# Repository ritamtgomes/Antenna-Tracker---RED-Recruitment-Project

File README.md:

# ESP32 Antenna Tracker

## Overview
This project is a **PCB-based antenna tracker** originally developed as a recruitment project for the **Rocket Experiment Division (RED)** at Instituto Superior Técnico. 

The system is designed to track a flying rocket in real time and orient an antenna towards it, minimizing telemetry loss during launches and flight operations. Tracking is achieved by computing the relative azimuth and elevation angles between the ground station and the rocket, and actuating two servo motors accordingly.

## System Architecture
1. The rocket transmits its position to the ground station
2. The tracker’s local GPS module provides its own position
3. The ESP32 computes Azimuth amd Elevation and converts these angles into PWM signals
4. The two servo motors rotate the antenna to maintain alignment with the rocket

## Hardware Specifications

### Core Components
- **Microcontroller**: ESP32-C3 SoC (Wi-Fi / Bluetooth capable)
- **GPS Module**: u-blox NEO-M9N-00B
- **Actuators**: 2 × High-torque servo motors (azimuth & elevation)
- **RF Receiver**: RFD868x (or compatible)
- **Power**: 2S Li-ion battery (7.4 V)
- On-board 5 V and 3.3 V regulation

### PCB
- Designed in KiCad
- Dimensions: 75 × 55 mm
- All components placed on the top layer

## Current Status
- **Hardware design**: Completed
- **PCB layout**: Ongoing improvements and minor revisions
- **Firmware**: In development
- **Assembly & testing**: Pending

## Future Improvements
- Improved PCB routing 
- Redundant antenna configurations (directional + omnidirectional)
- MAVLink integration

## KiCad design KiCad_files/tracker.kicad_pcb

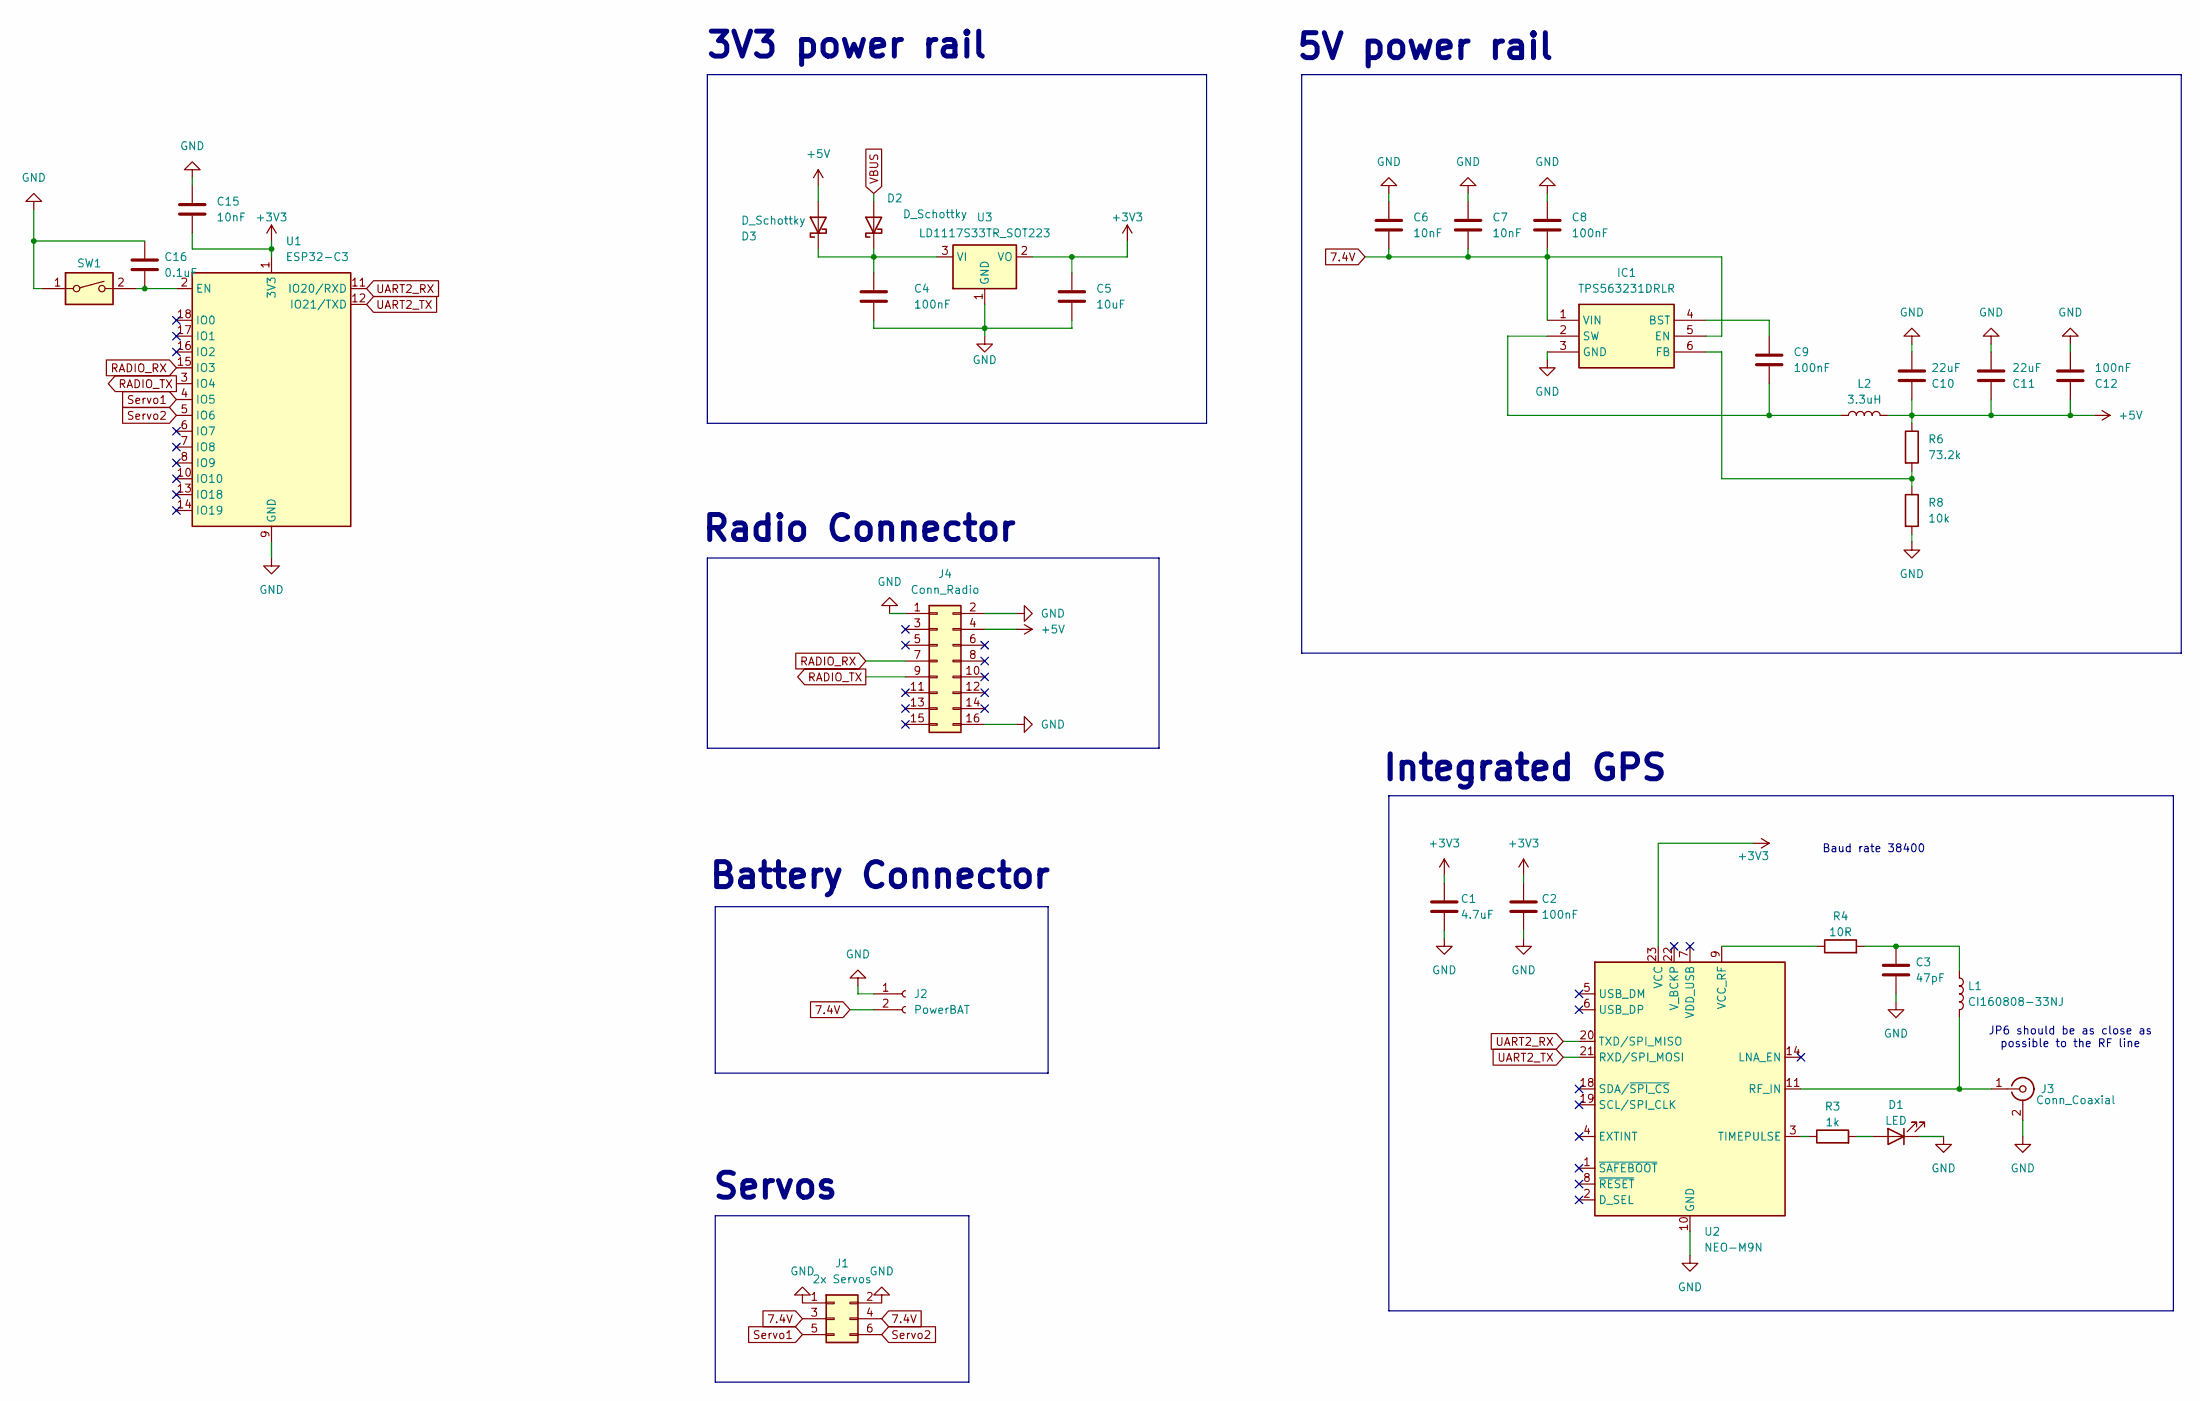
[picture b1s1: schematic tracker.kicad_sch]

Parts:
C1: 4.7uF; C_1206_3216Metric
C2, C4: 100nF; C_1206_3216Metric
C3: 47pF; C_1206_3216Metric
C5: 10uF; C_1206_3216Metric
C6, C7, C15: 10nF; C_0805_2012Metric_Pad1.18x1.45mm_HandSolder
C8, C9, C12: 100nF; C_0805_2012Metric_Pad1.18x1.45mm_HandSolder
C10, C11: 22uF; C_0805_2012Metric_Pad1.18x1.45mm_HandSolder
C16: 0.1uF; C_0805_2012Metric_Pad1.18x1.45mm_HandSolder
D1: LED; LED_1206_3216Metric
D2, D3: D_Schottky; D_0805_2012Metric_Pad1.15x1.40mm_HandSolder
IC1: TPS563231DRLR; SOTFL50P160X60-6N; Manufacturer_Part_Number TPS563231DRLR
J1: 2x Servos; PinHeader_2x03_P2.54mm_Horizontal
J2: PowerBAT; AMASS_XT30UPB-F_1x02_P5.0mm_Vertical
J3: Conn_Coaxial; U.FL_Molex_MCRF_73412-0110_Vertical
J4: Conn_Radio; PinSocket_2x08_P2.54mm_Vertical_SMD
L1: CI160808-33NJ; L_0603_1608Metric_Pad1.05x0.95mm_HandSolder
L2: 3.3uH; L_Vishay_IHLP-2020
R3: 1k; R_1206_3216Metric
R4: 10R; R_1206_3216Metric
R6: 73.2k; R_0402_1005Metric_Pad0.72x0.64mm_HandSolder
R8: 10k; R_0402_1005Metric_Pad0.72x0.64mm_HandSolder
SW1: SW_Push_1P1T_NO_CK_KSC6xxJ
U1: ESP32-C3; ESP32-C3-WROOM-02
U2: NEO-M9N; ublox_NEO
U3: LD1117S33TR_SOT223; SOT-223-3_TabPin2

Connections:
7.4V: C6.2, C7.2, C8.2, IC1.1 (VIN), IC1.5 (EN), J1.3, J1.4, J2.2
+3V3: C1.1, C2.1, C5.1, C15.2, U1.1 (3V3), U2.23 (VCC), U3.2 (VO)
+5V: C10.1, C11.1, C12.1, D3.2 (A), J4.4, L2.2, R6.1
GND: C1.2, C2.2, C3.2, C4.2, C5.2, C6.1, C7.1, C8.1, C10.2, C11.2, C12.2, C15.1, C16.2, D1.1 (K), IC1.3 (GND), J1.1, J1.2, J2.1, J3.2 (Ext), J4.1, J4.2, J4.16, R8.2, SW1.1, U1.9 (GND), U1.19 (GND), U2.10 (GND), U2.12 (GND), U2.13 (GND), U2.24 (GND), U3.1 (GND)
unnamed: C3.1, L1.1, R4.2
unnamed: D1.2 (A), R3.2
unnamed: C4.1, D2.1 (K), D3.1 (K), U3.3 (VI)
unnamed: C9.1, IC1.4 (BST)
unnamed: IC1.6 (FB), R6.2, R8.1
unnamed: C9.2, IC1.2 (SW), L2.1
unnamed: J3.1 (In), L1.2, U2.11 (RF_IN)
unnamed: C16.1, SW1.2, U1.2 (EN)
unnamed: R3.1, U2.3 (TIMEPULSE)
unnamed: R4.1, U2.9 (VCC_RF)
RADIO_RX: J4.7, U1.15 (IO3)
RADIO_TX: J4.9, U1.3 (IO4)
Servo1: J1.5, U1.4 (IO5)
Servo2: J1.6, U1.5 (IO6)
UART2_RX: U1.11 (IO20/RXD), U2.20 (TXD/SPI_MISO)
UART2_TX: U1.12 (IO21/TXD), U2.21 (RXD/SPI_MOSI)
VBUS: D2.2 (A)

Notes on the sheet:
Integrated GPS
Servos
Baud rate 38400
JP6 should be as close as possible to the RF line
3V3 power rail
Radio Connector
5V power rail
Battery Connector

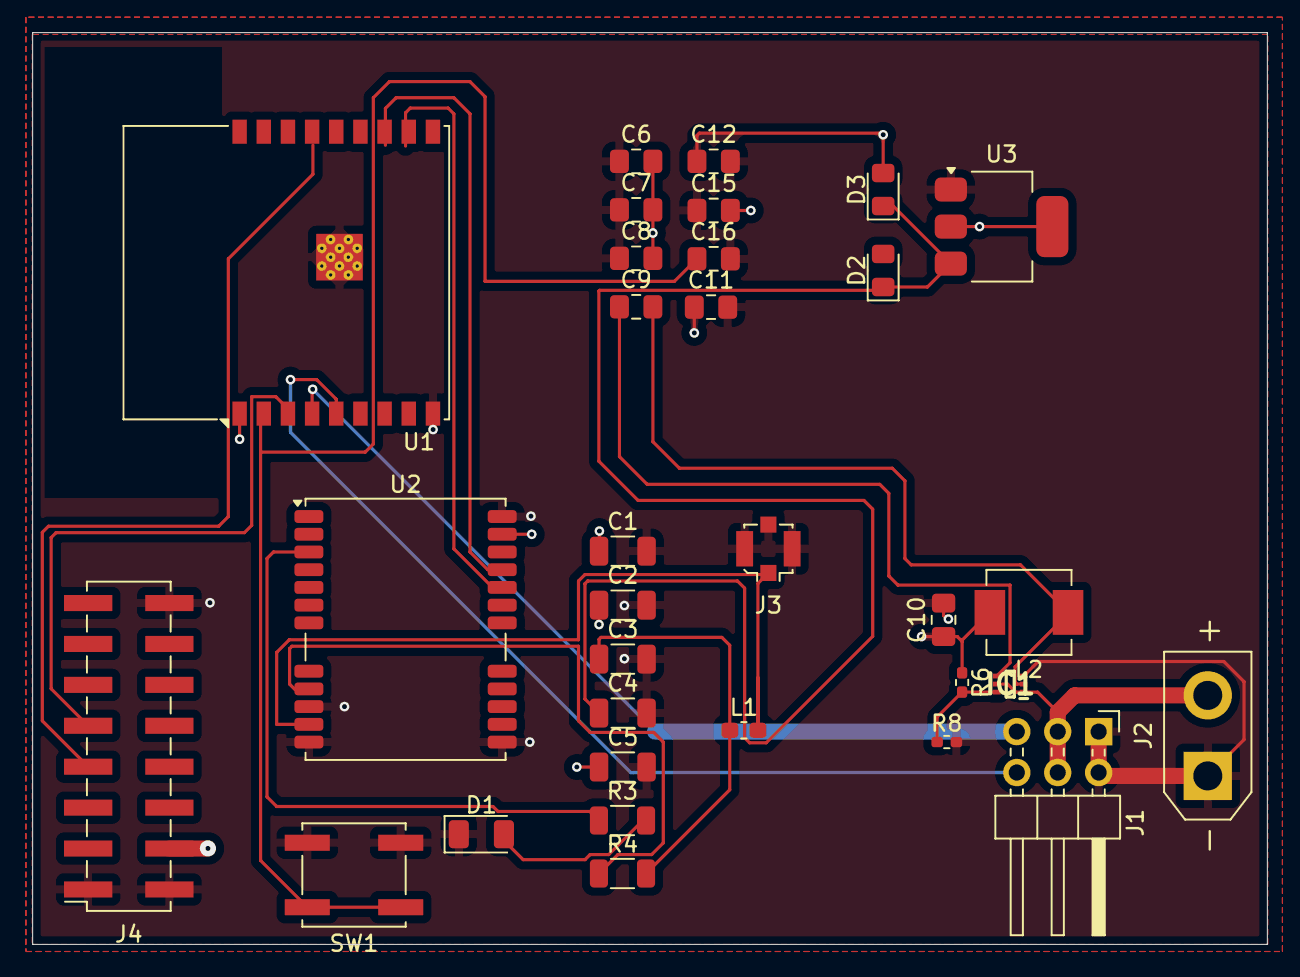
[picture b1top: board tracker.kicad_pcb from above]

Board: 4 copper layers, 76.7 x 56.6 mm, 32 parts (0 on the bottom side), 20 nets.

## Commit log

2026-02-09 add project README
2026-02-09 README updates
2026-02-10 pcb: rework layout and board outline (v2)
